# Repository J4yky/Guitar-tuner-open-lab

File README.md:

# Guitar-tuner-open-lab
### Twórcy
- Jakub Naumowicz
- Aleksandra Kromołowska
- Marta Kresińska
- Filip Krauz-Damski

## Opis projektu
Projekt automatycznego stroika do gitary 

# Praca w grupie !!!!!!!!!!!!!!!!!
1. Pracując nad czymkolwiek - pracujemy na osobnym branchu.
2. Merge do maina dopiero po skończeniu etapu na swoim branchu i ZATWIERDZONY PRZEZ DRUGĄ OSOBĘ.
   Czyli jeśli chcę dodać zmiany z mojego brancha na main to ja robię pull request a ktoś inny go sprawdza i zatwierdza.

# Struktura plików
Pusty folder nie jest trackowany przez git więc nie mogłem ich dodać. Natomiast jeśli ktoś będzie wrzucał np. wykres z LTSpice
albo aktualizacje raportu z Overleaf'a JAKO PIERWSZY, to niech stworzy folder (jak poniżej) i dopiero w nim dodaje rzeczy i potem
niech doda CAŁY FOLDER, żeby finalnie pliki w repozytorium wyglądały według poniższego schematu:
- |
- |--- graphs
- |--- LTSpice
- |--- KiCAD
- |--- 3D_Model
- |--- repo
- |--- others
- |--- .gitignore
- |--- README.md

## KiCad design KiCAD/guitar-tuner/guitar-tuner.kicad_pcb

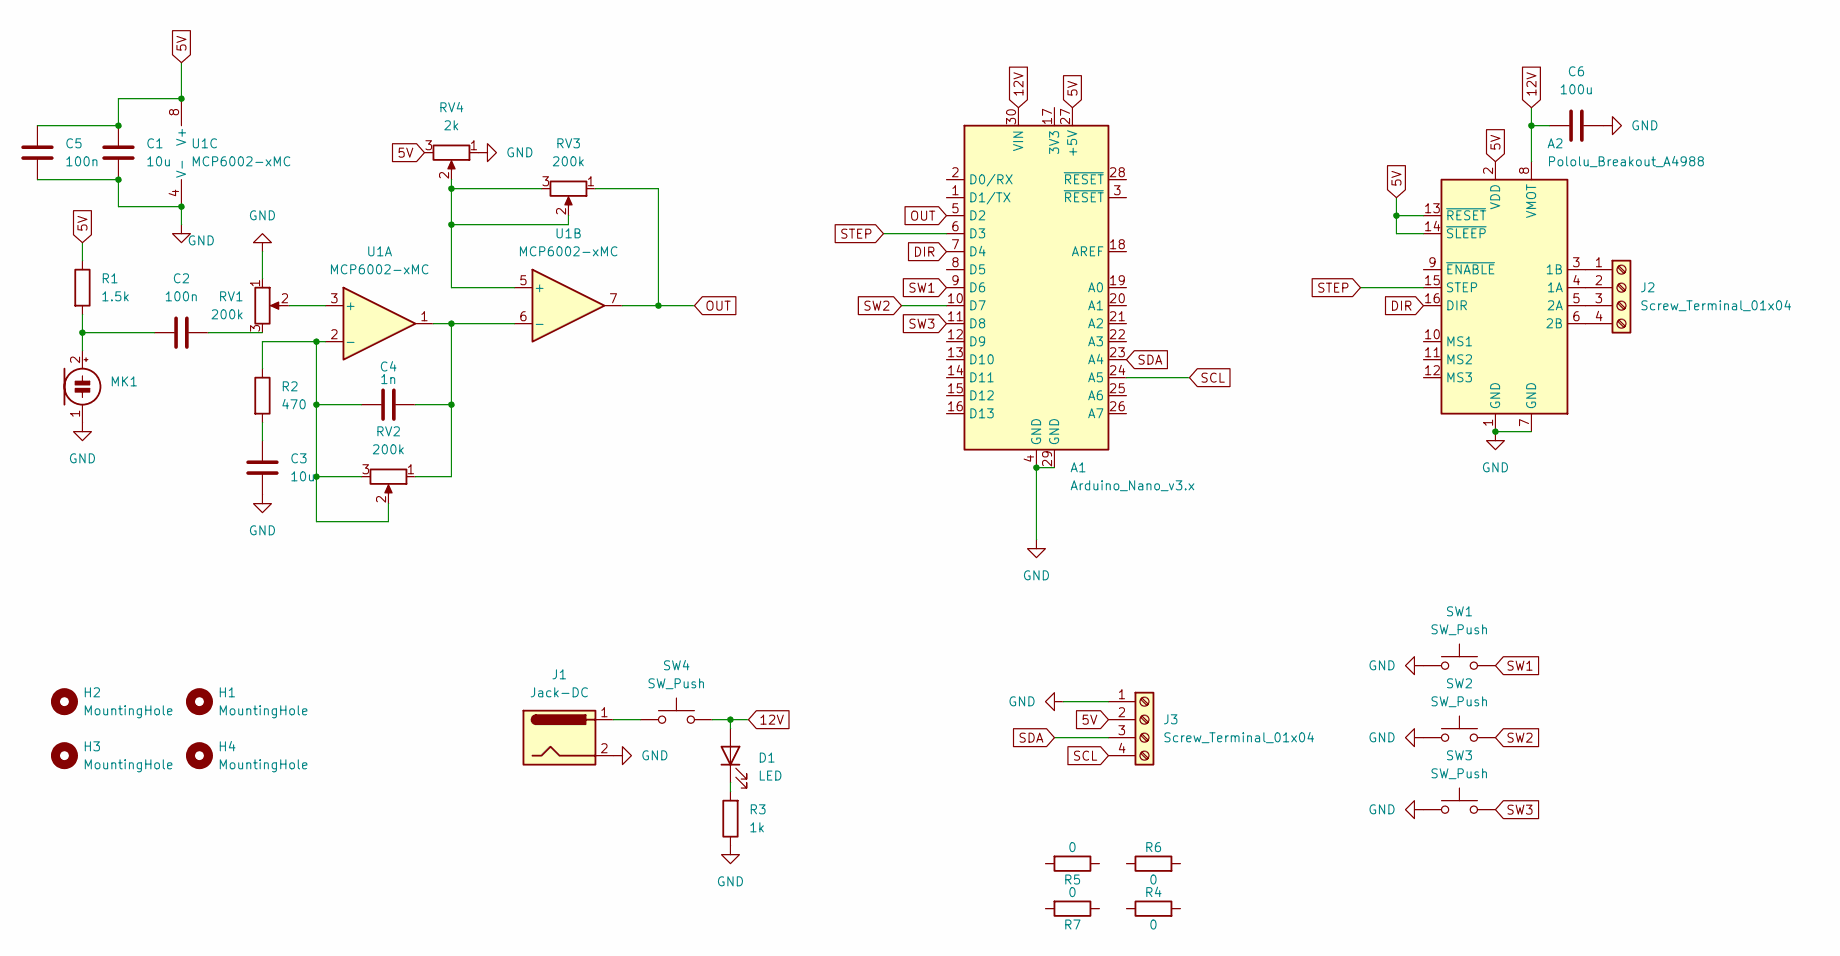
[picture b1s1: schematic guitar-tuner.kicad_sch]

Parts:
A1: Arduino_Nano_v3.x; Arduino_Nano
A2: Pololu_Breakout_A4988; Pololu_Breakout-16_15.2x20.3mm
C1, C3: 10u; CP_Radial_D5.0mm_P2.50mm
C2, C5: 100n; C_0805_2012Metric
C4: 1n; C_0805_2012Metric
C6: 100u; C_Radial_D5.0mm_H11.0mm_P2.00mm
D1: LED; LED_D5.0mm
H1, H2, H3, H4: MountingHole; MountingHole_2.2mm_M2
J1: Jack-DC; BarrelJack_SwitchcraftConxall_RAPC10U_Horizontal
J2, J3: Screw_Terminal_01x04; TerminalBlock_Xinya_XY308-2.54-4P_1x04_P2.54mm_Horizontal
MK1: Microphone_Condenser; SolderWire-0.1sqmm_1x02_P3.6mm_D0.4mm_OD1mm
R1: 1.5k; R_0805_2012Metric
R2: 470; R_0805_2012Metric
R3: 1k; R_0805_2012Metric
R4, R6: 0; R_1206_3216Metric
R5, R7: 0; R_2010_5025Metric
RV1, RV2, RV3: 200k; Potentiometer_Bourns_3386P_Vertical
RV4: 2k; Potentiometer_Bourns_3386P_Vertical
SW1, SW2, SW3: SW_Push; SW_PUSH_6mm
SW4: SW_Push; SW_Push_2P2T_Toggle_CK_PVA2xxH1xxxxxxV2
U1: MCP6002-xMC; DIP-8_W7.62mm

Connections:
5V: A1.27 (+5V), A2.2 (VDD), A2.13 (~RESET), A2.14 (~SLEEP), C1.2, C5.2, J3.2, R1.1, R7.1, R7.2, RV4.3, U1.8 (V+)
12V: A1.30 (VIN), A2.8 (VMOT), C6.2, D1.2 (A), SW4.2
DIR: A1.7 (D4), A2.16 (DIR)
GND: A1.4 (GND), A1.29 (GND), A2.1 (GND), A2.7 (GND), C1.1, C3.1, C5.1, C6.1, J1.2, J3.1, MK1.1 (-), R3.1, R4.1, R4.2, R5.1, R5.2, R6.1, R6.2, RV1.1, RV4.1, SW1.1, SW2.1, SW3.1, U1.4 (V-), U1.9 (V-)
unnamed: A2.4 (1A), J2.2
unnamed: A2.3 (1B), J2.1
unnamed: A2.5 (2A), J2.3
unnamed: A2.6 (2B), J2.4
unnamed: C2.2, RV1.3
unnamed: C3.2, R2.2
unnamed: D1.1 (K), R3.2
unnamed: J1.1, SW4.1
unnamed: C2.1, MK1.2 (+), R1.2
unnamed: RV1.2, U1.3 (+)
unnamed: C4.2, R2.1, RV2.2, RV2.3, U1.2 (-)
unnamed: RV3.2, RV3.3, RV4.2, U1.5 (+)
unnamed: C4.1, RV2.1, U1.1, U1.6 (-)
OUT: A1.5 (D2), RV3.1, U1.7
SCL: A1.24 (A5), J3.4
SDA: A1.23 (A4), J3.3
STEP: A1.6 (D3), A2.15 (STEP)
SW1: A1.9 (D6), SW1.2
SW2: A1.10 (D7), SW2.2
SW3: A1.11 (D8), SW3.2

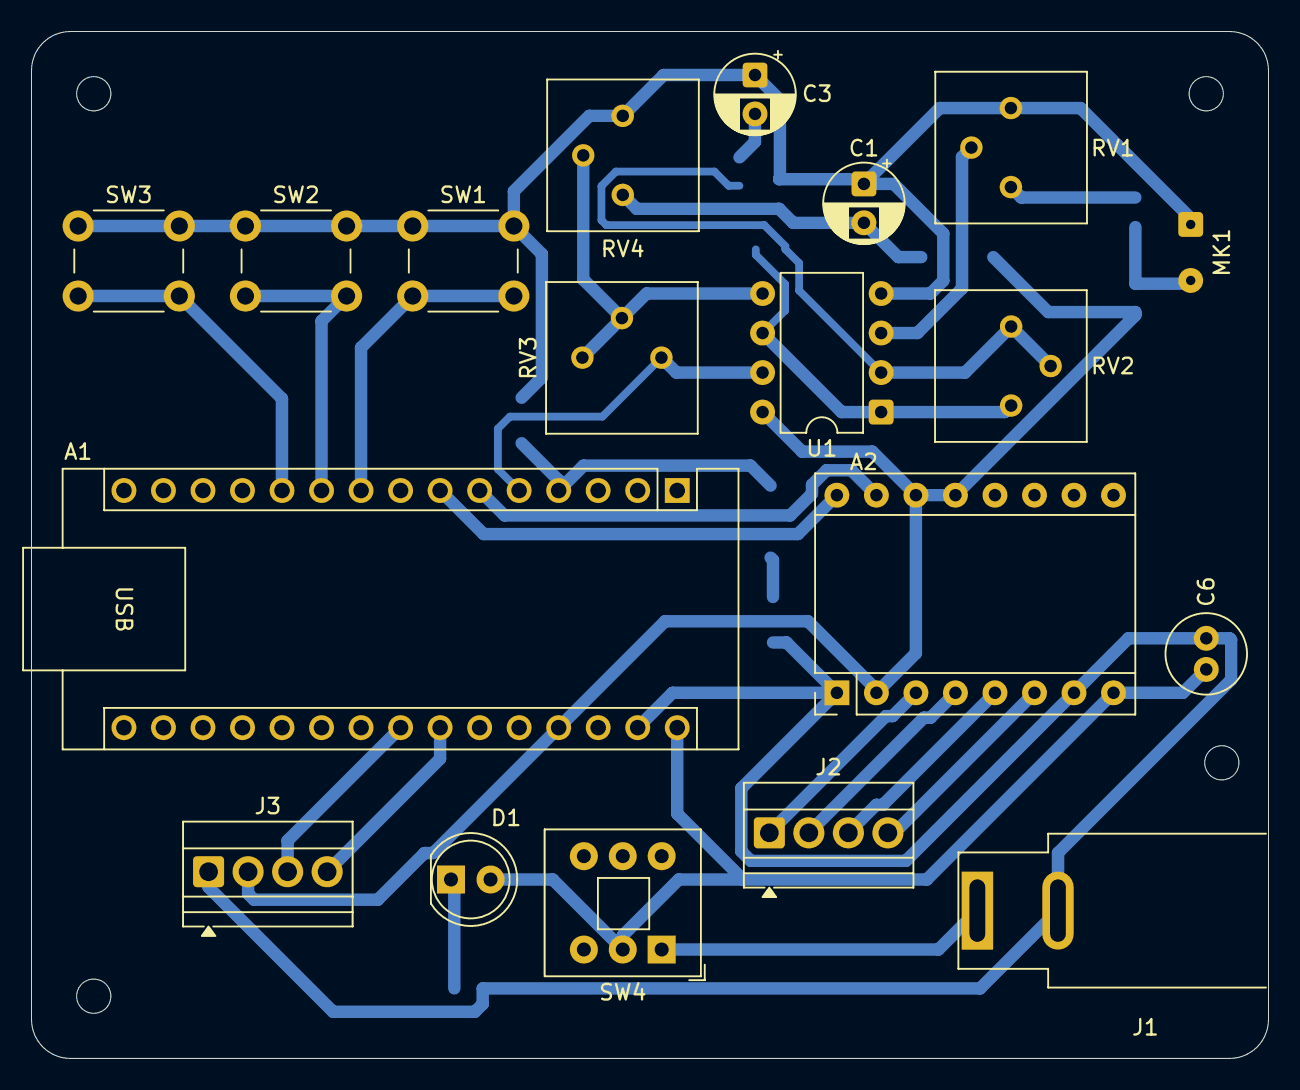
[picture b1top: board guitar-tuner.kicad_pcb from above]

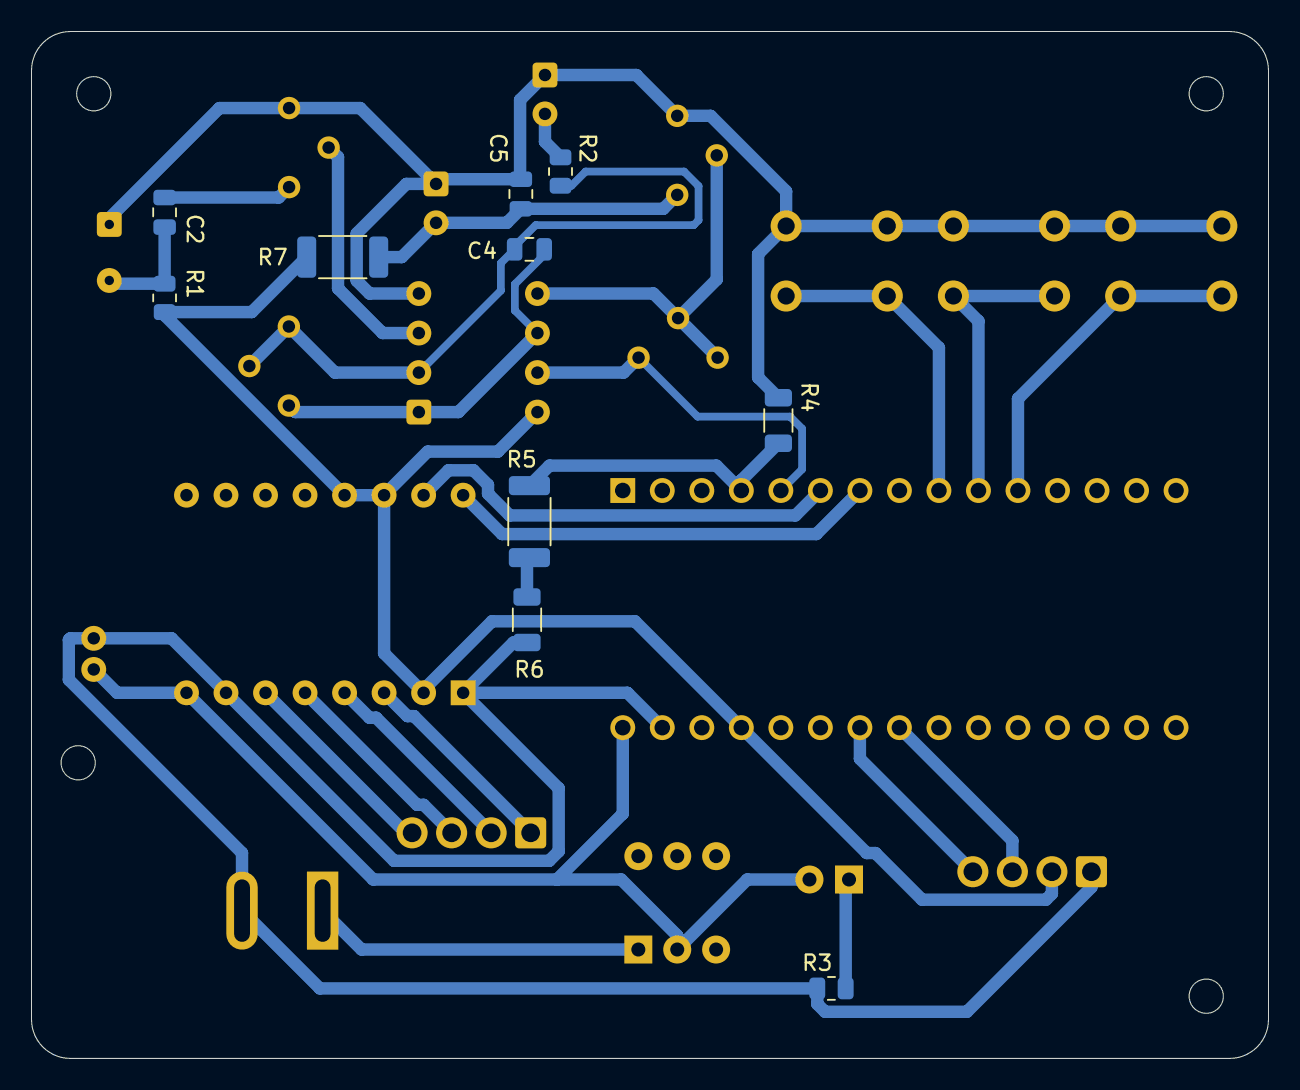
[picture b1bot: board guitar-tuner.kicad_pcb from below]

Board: 2 copper layers, 79.5 x 66.0 mm, 33 parts (10 on the bottom side), 24 nets.

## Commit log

2026-03-16 README added
2026-03-16 added gitignore
2026-03-16 Update README with group work and file structure guidelines
    Added guidelines for group work and file structure.
2026-03-16 Fix typo in README.md section header
2026-03-16 Add image to README for collaboration guidelines
    Added an image to the collaboration guidelines section.
2026-03-16 Diagram added
2026-03-17 Reworked file structure
2026-03-21 Electret mic amp with schmitt trigger scheme
2026-03-30 Create .gitignore for project dependencies
    Add common ignore patterns for KiCad, LTSpice, and Arduino.
2026-03-30 KiCAD scheme
2026-03-30 Added potenciometers
2026-04-16 Board_v1
2026-04-20 Board_v2
